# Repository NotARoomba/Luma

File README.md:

<h1 align="center">
  <br>
  
  <br>
  Luma
  <br>
</h1>

<h4 align="center">
A Minecraft inspired lantern with bluetooth!

</h4>

<div align="center">

</div>

<p align="center">
  <a href="#key-features">Key Features</a> •
  <a href="#case-and-cad">Case & CAD</a> •
  <a href="#pcb">PCB</a> •
  <a href="#bom">BOM</a> •
  <a href="#credits">Credits</a> •
  <a href="#license">License</a>
</p>

## Key Features

- Bluetooth/Wifi capabilitis
- Bright configurable LED's
- Easy to assemble case
- App to control/change colors

## Case and CAD

The case includes:

- 3D printed parts: The base, walls, top, and chain
- Glueable inserts and acrylic panes

Designed in Fusion 360.

## PCB

Designed in KiCad. Notable points:

- ESP32-WROOM-32E for bluetooth support
- LiPo battery charging circuit
- USB-C
- LED Header to add custom LED's

### Main Board

## BOM

| Item             | Price (USD) | Source                                                                                                                                                                                                                                                                                                          |
| ---------------- | ----------- | --------------------------------------------------------------------------------------------------------------------------------------------------------------------------------------------------------------------------------------------------------------------------------------------------------------- |
| PCB              | 134.77      | JLCPCB                                                                                                                                                                                                                                                                                                          |
| 3D Printed Parts | 0.00        | (already have a 3D printer)                                                                                                                                                                                                                                                                                     |
| Acrylic Panes    | 0.00        | (already have)                                                                                                                                                                                                                                                                                                  |
| LED Strip        | 0.00        | (already have)                                                                                                                                                                                                                                                                                                  |
| LiPo 1200mAh     | 12.00       | [Online Marketplace (Aliexpress takes 1 month)](https://articulo.mercadolibre.com.co/MCO-897219547-bateria-37v-1200mah-litio-lipo-35-x-6cm-ancho-05cm-_JM#polycard_client=search-nordic&position=31&search_layout=stack&type=item&tracking_id=64c5a1d6-adab-4203-b581-c1839af5c176&wid=MCO897219547&sid=search) |
| **Total**        | 146.77      |                                                                                                                                                                                                                                                                                                                 |

## Credits

This project uses:

- [KiCad](https://www.kicad.org/)
- [VSCode](https://code.visualstudio.com/)
- [Fusion 360](https://www.autodesk.com/products/fusion-360/overview)

## You may also like...

- [Niveles De Niveles](https://github.com/NotARoomba/NivelesDeNiveles) – Real-time flood alert app
- [Linea](https://github.com/NotARoomba/Linea) – An EMR tablet
- [Tamaki](https://github.com/NotARoomba/Tamaki) – A cute HackPad

## License

MIT

---

> [notaroomba.dev](https://notaroomba.dev) &nbsp;&middot;&nbsp;
> GitHub [@NotARoomba](https://github.com/NotARoomba)

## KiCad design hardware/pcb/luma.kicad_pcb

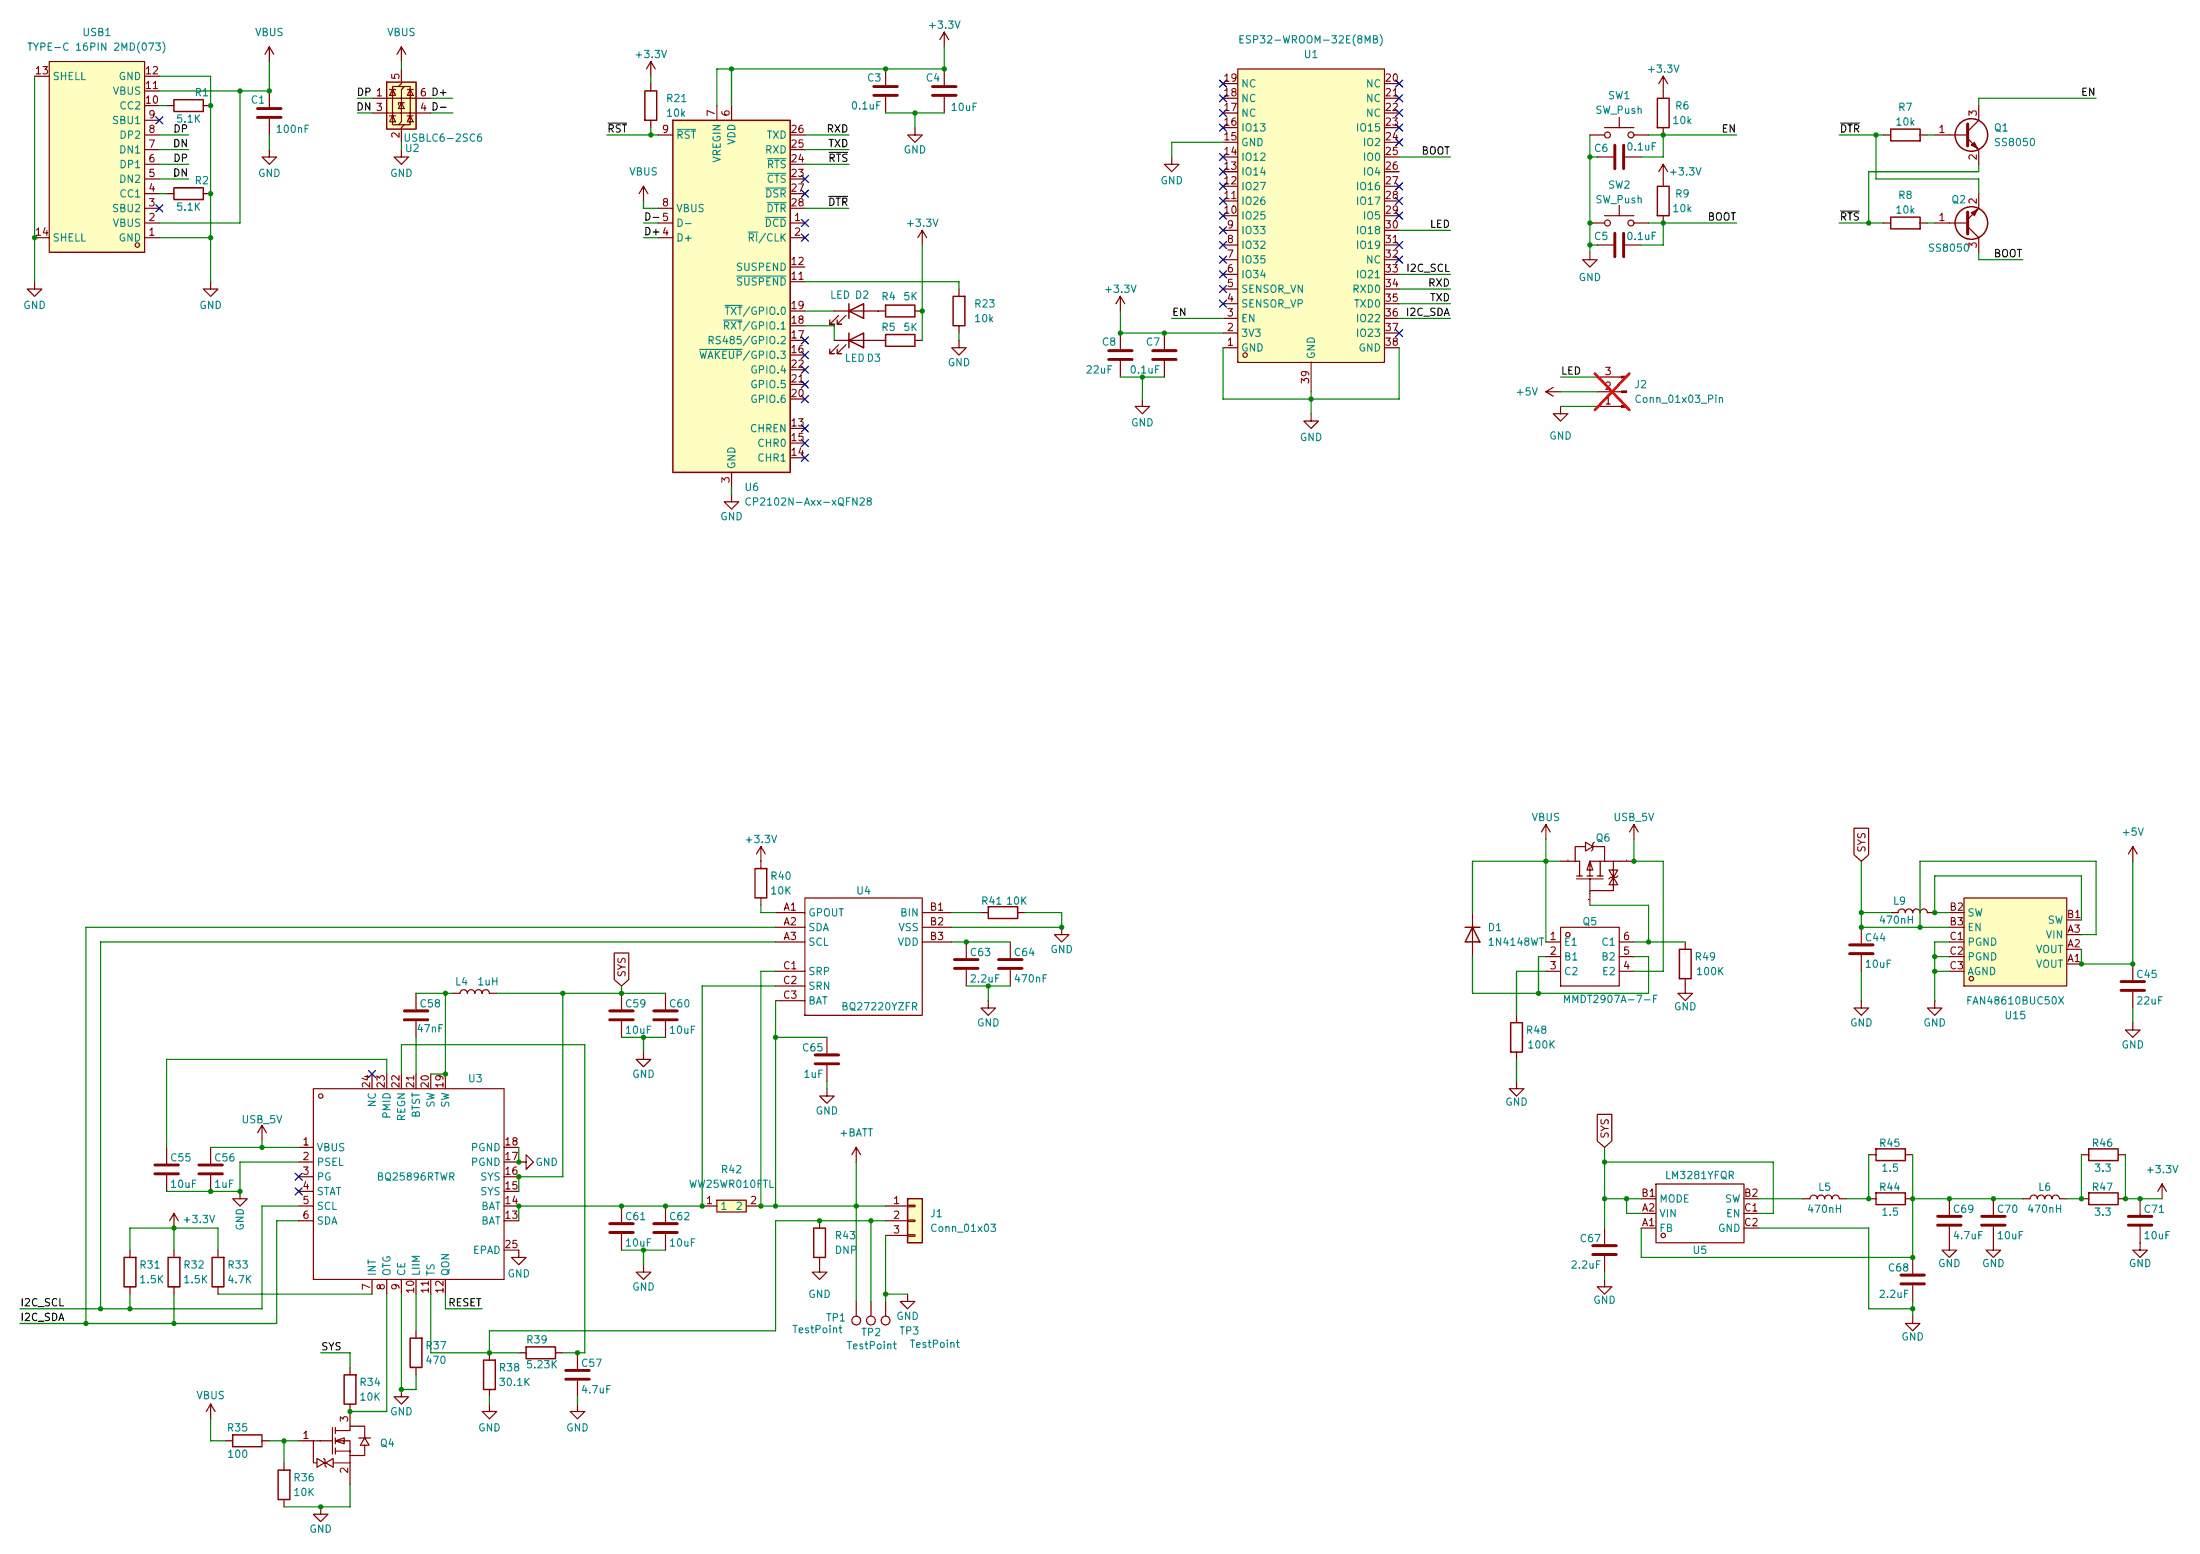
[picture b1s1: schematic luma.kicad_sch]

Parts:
C1: 100nF; C_0603_1608Metric
C3, C5, C6, C7: 0.1uF; C_0402_1005Metric
C4: 10uF; C_0603_1608Metric
C8: 22uF; C_0603_1608Metric
C44, C55, C59, C60, C61, C62, C70, C71: 10uF; C_0402_1005Metric
C45: 22uF; C_0402_1005Metric
C56, C65: 1uF; C_0402_1005Metric
C57, C69: 4.7uF; C_0402_1005Metric
C58: 47nF; C_0402_1005Metric
C63, C67, C68: 2.2uF; C_0402_1005Metric
C64: 470nF; C_0402_1005Metric
D1: 1N4148WT; D_SOD-523
D2, D3: LED; LED_0201_0603Metric
J1: Conn_01x03; JST_EH_S3B-EH_1x03_P2.50mm_Horizontal; LCSC C263754
J2: Conn_01x03_Pin; PinHeader_1x03_P2.00mm_Vertical; not fitted
L4: 1uH; L_0603_1608Metric
L5, L6: 470nH; L_0603_1608Metric
L9: 470nH; L_Murata_DFE201610P; LCSC C882980
Q1, Q2: SS8050; SOT-23; MPN SS8050-HF
Q4: SOT-523-3_L1.6-W0.8-P1.00-LS1.6-BR; Manufacturer Part DMN313DLT-7; LCSC C155524
Q5: SOT-363_L2.0-W1.3-P0.65-LS2.1-BL; Manufacturer Part MMDT2907A-7-F; LCSC C460232
Q6: SOT-23-3_L2.9-W1.3-P1.90-LS2.4-BR; Manufacturer Part DMP1045U-7; LCSC Part Name 1个P沟道 耐压:12V 电流:4A
R1, R2: 5.1K; R_0402_1005Metric
R4, R5: 5K; R_0402_1005Metric; MPN CRCW040210K0FKED
R6, R7, R8, R9, R21, R23: 10k; R_0402_1005Metric; MPN CRCW040210K0FKED
R31, R32: 1.5K; R_0402_1005Metric
R33: 4.7K; R_0402_1005Metric
R34, R36, R40, R41: 10K; R_0402_1005Metric
R35: 100; R_0402_1005Metric
R37: 470; R_0402_1005Metric
R38: 30.1K; R_0402_1005Metric
R39: 5.23K; R_0402_1005Metric
R42: WW25WR010FTL; R2512; LCSC Part C171418
R43: DNP; R_0402_1005Metric
R44, R45: 1.5; R_0402_1005Metric
R46, R47: 3.3; R_0402_1005Metric
R48, R49: 100K; R_0402_1005Metric
SW1, SW2: SW_Push; SW-SMD_L3.9-W3.0-P4.45; LCSC C720477
TP1, TP2, TP3: TestPoint; TestPoint_Pad_1.5x1.5mm
U1: ESP32-WROOM-32E(8MB); WIFI-SMD_ESP32-WROOM-32E; LCSC Part C701342
U2: USBLC6-2SC6; SOT-666; MPN USBLC6-2SC6
U3: QFN-24_L4.0-W4.0-P0.50-TL-EP2.7; Manufacturer Part BQ25896RTWR; LCSC C181475
U4: DSBGA-9_L1.7-W1.6-R3-C3-P0.50-BL; Manufacturer Part BQ27220YZFR; LCSC C528617
U5: DSBGA-6_L1.4-W1.1-R3-C2-P0.40-BL; Manufacturer Part LM3281YFQR; LCSC C2070970
U6: CP2102N-Axx-xQFN28; QFN-28-1EP_5x5mm_P0.5mm_EP3.35x3.35mm; LCSC C964632
U15: FAN48610BUC50X; WLCSP-9_L1.2-W1.2-R3-C3-P0.40-BL; LCSC Part C890711
USB1: TYPE-C 16PIN 2MD(073); USB-C-SMD_TYPE-C-6PIN-2MD-073; LCSC Part C2765186

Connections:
+3.3V: C3.1, C4.1, C7.1, C8.1, C71.1, R4.1, R5.1, R6.1, R9.1, R21.1, R31.2, R32.2, R33.2, R40.2, R46.1, R47.1, U1.2 (3V3), U6.6 (VDD), U6.7 (VREGIN)
+5V: C45.1, J2.2, U15.A1 (VOUT), U15.A2 (VOUT)
+BATT: C65.1, J1.1, R42.2, TP1.1, U4.C1 (SRP), U4.C3 (BAT)
/BOOT: C5.2, Q2.3 (C), R9.2, SW2.2, U1.25 (IO0)
/D+: U2.6 (I/O1), U6.4 (D+)
/D-: U2.4 (I/O2), U6.5 (D-)
/DN: U2.3 (I/O2), USB1.5 (DN2), USB1.7 (DN1)
/DP: U2.1 (I/O1), USB1.6 (DP1), USB1.8 (DP2)
/EN: C6.2, Q1.3 (C), R6.2, SW1.2, U1.3 (EN)
/I2C_SCL: R31.1, U1.33 (IO21), U3.5 (SCL), U4.A3 (SCL)
/I2C_SDA: R32.1, U1.36 (IO22), U3.6 (SDA), U4.A2 (SDA)
/LED: J2.3, U1.30 (IO18)
/RESET: U3.12 (QON)
/RXD: U1.34 (RXD0), U6.26 (TXD)
/TXD: U1.35 (TXD0), U6.25 (RXD)
/~DTR: Q2.2 (E), R7.1, U6.28 (~DTR)
/~RST: R21.2, U6.9 (~RST)
/~RTS: Q1.2 (E), R8.1, U6.24 (~RTS)
GND: C1.2, C3.2, C4.2, C5.1, C6.1, C7.2, C8.2, C44.2, C45.2, C55.2, C56.2, C57.2, C59.2, C60.2, C61.2, C62.2, C63.2, C64.2, C65.2, C67.2, C68.2, C69.2, C70.2, C71.2, J1.3, J2.1, Q4.2 (S), R1.2, R2.2, R23.1, R36.1, R37.1, R38.1, R41.1, R43.2, R48.2, R49.2, SW1.1, SW2.1, TP3.1, U1.1 (GND), U1.15 (GND), U1.38 (GND), U1.39 (GND), U2.2 (GND), U3.2 (PSEL), U3.9 (CE), U3.17 (PGND), U3.18 (PGND), U3.25 (EPAD), U4.B2 (VSS), U5.C2 (GND), U6.3 (GND), U6.29 (GND), U15.C1 (PGND), U15.C2 (PGND), U15.C3 (AGND), USB1.1 (GND), USB1.12 (GND), USB1.13 (SHELL), USB1.14 (SHELL)
unnamed: C58.1, L4.1, U3.19 (SW), U3.20 (SW)
unnamed: D1.2 (A), Q5.2 (B1), Q5.5 (B2)
unnamed: D2.2 (A), R4.2
unnamed: D2.1 (K), U6.19 (~TXT/GPIO.0)
unnamed: D3.2 (A), R5.2
unnamed: D3.1 (K), U6.18 (~RXT/GPIO.1)
unnamed: J1.2, R38.2, R39.2, R43.1, TP2.1, U3.11 (TS)
unnamed: L5.2, R44.2, R45.2
unnamed: L6.2, R46.2, R47.2
unnamed: L9.2, U15.B1 (SW), U15.B2 (SW)
unnamed: Q1.1 (B), R7.2
unnamed: Q2.1 (B), R8.2
unnamed: Q4.3 (D), R34.1, U3.8 (OTG)
unnamed: Q4.1 (G), R35.1, R36.2
unnamed: Q5.6 (C1), Q6.1 (G), R49.1
unnamed: Q5.3 (C2), R48.1
unnamed: C58.2, U3.21 (BTST)
unnamed: R33.1, U3.7 (INT)
unnamed: R37.2, U3.10 (LIIM)
unnamed: C55.1, U3.23 (PMID)
unnamed: C57.1, R39.1, U3.22 (REGN)
unnamed: R41.2, U4.B1 (BIN)
unnamed: R40.1, U4.A1 (GPOUT)
unnamed: C61.1, C62.1, R42.1, U3.13 (BAT), U3.14 (BAT), U4.C2 (SRN)
unnamed: C63.1, C64.1, U4.B3 (VDD)
unnamed: C68.1, C69.1, C70.1, L6.1, R44.1, R45.1, U5.A1 (FB)
unnamed: L5.1, U5.B2 (SW)
unnamed: R23.2, U6.11 (~SUSPEND)
unnamed: R2.1, USB1.4 (CC1)
unnamed: R1.1, USB1.10 (CC2)
SYS: C44.1, C59.1, C60.1, C67.1, L4.2, L9.1, R34.2, U3.15 (SYS), U3.16 (SYS), U5.A2 (VIN), U5.B1 (MODE), U5.C1 (EN), U15.A3 (VIN), U15.B3 (EN)
USB_5V: C56.1, Q5.4 (E2), Q6.2 (S), U3.1 (VBUS)
VBUS: C1.1, D1.1 (K), Q5.1 (E1), Q6.3 (D), R35.2, U2.5 (VBUS), U6.8 (VBUS), USB1.2 (VBUS), USB1.11 (VBUS)

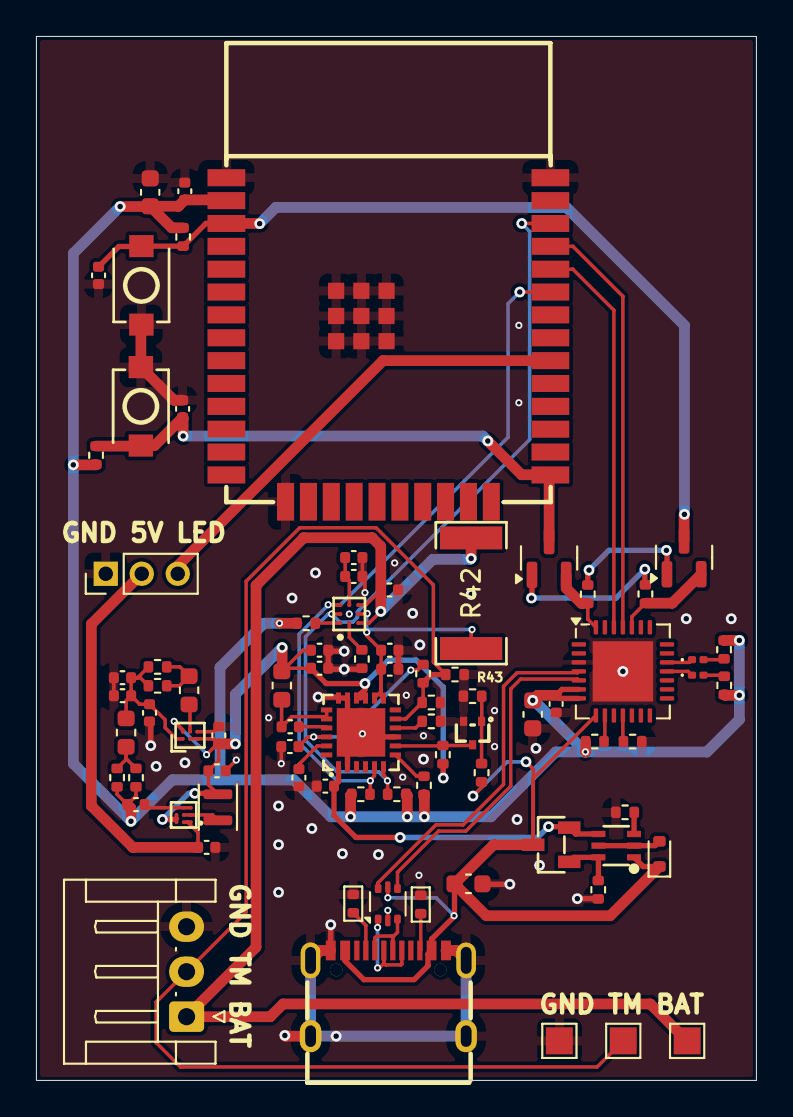
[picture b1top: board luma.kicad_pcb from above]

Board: 2 copper layers, 40.0 x 58.0 mm, 81 parts (0 on the bottom side), 51 nets.

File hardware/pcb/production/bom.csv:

Designator,Footprint,Quantity,Value,LCSC Part #
C1,0603,1,100nF,
"C3, C5, C6, C7",0402,4,0.1uF,
C4,0603,1,10uF,
"C44, C55, C59, C60, C61, C62, C70, C71",0402,8,10uF,
C45,0402,1,22uF,
"C56, C65",0402,2,1uF,
"C57, C69",0402,2,4.7uF,
C58,0402,1,47nF,
"C63, C67, C68",0402,3,2.2uF,
C64,0402,1,470nF,
C8,0603,1,22uF,
D1,D_SOD-523,1,1N4148WT,
"D2, D3",0201,2,LED,
J1,JST_EH_S3B-EH_1x03_P2.50mm_Horizontal,1,Conn_01x03,C263754
J2,PinHeader_1x03_P2.00mm_Vertical,1,Conn_01x03_Pin,
L4,0603,1,1uH,
"L5, L6",0603,2,470nH,
L9,L_Murata_DFE201610P,1,470nH,C882980
"Q1, Q2",SOT-23,2,SS8050,SS8050-HF
Q4,SOT-523-3_L1.6-W0.8-P1.00-LS1.6-BR,1,~,C155524
Q5,SOT-363_L2.0-W1.3-P0.65-LS2.1-BL,1,~,C460232
Q6,SOT-23-3_L2.9-W1.3-P1.90-LS2.4-BR,1,~,C177033
"R1, R2",0402,2,5.1K,
"R21, R23, R6, R7, R8, R9",0402,6,10k,CRCW040210K0FKED
"R31, R32",0402,2,1.5K,
R33,0402,1,4.7K,
"R34, R36, R40, R41",0402,4,10K,
R35,0402,1,100,
R37,0402,1,470,
R38,0402,1,30.1K,
R39,0402,1,5.23K,
"R4, R5",0402,2,5K,CRCW040210K0FKED
R42,R2512,1,WW25WR010FTL,C171418
R43,0402,1,DNP,
"R44, R45",0402,2,1.5,
"R46, R47",0402,2,3.3,
"R48, R49",0402,2,100K,
"SW1, SW2",SW-SMD_L3.9-W3.0-P4.45,2,SW_Push,
"TP1, TP2, TP3",TestPoint_Pad_1.5x1.5mm,3,TestPoint,
U1,WIFI-SMD_ESP32-WROOM-32E,1,ESP32-WROOM-32E(8MB),C701342
U15,WLCSP-9_L1.2-W1.2-R3-C3-P0.40-BL,1,FAN48610BUC50X,C890711
U2,SOT-666,1,USBLC6-2SC6,USBLC6-2SC6
U3,QFN-24_L4.0-W4.0-P0.50-TL-EP2.7,1,~,C181475
U4,DSBGA-9_L1.7-W1.6-R3-C3-P0.50-BL,1,~,C528617
U5,DSBGA-6_L1.4-W1.1-R3-C2-P0.40-BL,1,~,C2070970
U6,QFN-28-1EP_5x5mm_P0.5mm_EP3.35x3.35mm,1,CP2102N-Axx-xQFN28,
USB1,USB-C-SMD_TYPE-C-6PIN-2MD-073,1,TYPE-C 16PIN 2MD(073),C2765186

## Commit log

2025-07-18 adds schmatic ansd sart of boeard
2025-07-18 lock
2025-07-18 added stuff
2025-07-21 finished!
2025-07-21 added render
2025-07-22 name change
2025-07-22 astuff
2025-07-26 added bottom insets
2025-07-26 prod
2025-07-30 fix pcb placement
2025-07-30 adddd winsow and insets
2025-07-30 udpated with window
2025-08-14 added tolerances an finished build
2025-08-19 start
2025-08-19 start of app
2025-08-19 addd tuff
2025-08-20 commit stuff
2025-08-21 stuff
2025-08-26 before ble
